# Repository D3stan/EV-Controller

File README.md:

# EV-Controller

This project is an ESP8266/ESP32-based exhaust valve controller for motorcycles. It offers real-time monitoring and configuration through a web interface, utilizing WebSockets for live data communication. The core functionality is to control the motorcycle's exhaust valve based on configurable RPM thresholds.

<table>
  <tr>
    <td>
      <br>
      
    </td>
    <td>
      
    </td>
  </tr>
</table>

## Features

- RPM-based exhaust valve control with configurable opening and closing thresholds.
- Web interface for real-time RPM monitoring and settings adjustment.
- WiFi Access Point (AP) mode for initial setup and configuration.
- WiFi Station (STA) mode to connect to an existing wireless network.
- Secure Over-the-Air (OTA) updates for both firmware and filesystem.
- Manual override for valve control directly from the web interface.

## Hardware Construction

To build the hardware, you will need to manufacture the PCB and source the electronic components.

### 1. PCB Manufacturing

The Gerber files required for PCB production are located in the `pcb/production/gerber.zip` archive. You can upload this file to any PCB manufacturer of your choice.

### 2. Component Sourcing

The list of all necessary components (Bill of Materials) is available in the `pcb/production/bom.csv` file. This file can be used to order parts from electronic component distributors.

### 3. Assembly

Solder the components onto the manufactured PCB. For component placement and orientation, please refer to the following files:

- **Schematic:** `pcb/schema.pdf`
- **KiCad Project:** `pcb/Rave-Controller.kicad_pro` (can be opened with KiCad)

For automated pick-and-place assembly, the `pcb/production/positions.csv` file is also provided.

## Firmware Installation

The firmware is built using PlatformIO.

### Prerequisites

- [Visual Studio Code](https://code.visualstudio.com/)
- [PlatformIO IDE extension](https://platformio.org/install/ide?install=vscode) for VS Code

### Build and Upload

1.  Clone this repository to your local machine.
2.  Open the cloned repository folder in Visual Studio Code.
3.  PlatformIO will automatically detect the `platformio.ini` file and prompt you to install the required project dependencies.
4.  Once dependencies are installed, select the correct environment for your board (e.g., `d1_mini`).
5.  Use the PlatformIO "Upload" task to build and flash the firmware to your device. Alternatively, you can run the following command from the integrated terminal:
    ```bash
    pio run -e d1_mini --target upload
    ```

## Initial Setup

1.  On the first boot, the device will create a Wi-Fi Access Point. The default SSID and password can be found in the source code (`data/config.json`).
2.  Connect your computer or smartphone to this Wi-Fi network.
3.  Open a web browser and navigate to the device's default IP address, which is `42.42.42.42`.
4.  From the web interface, you can configure your home Wi-Fi credentials (SSID and password) and set the desired RPM thresholds for the exhaust valve operation.
5.  After saving the new settings, the device will restart, connect to your specified Wi-Fi network, and begin normal operation.

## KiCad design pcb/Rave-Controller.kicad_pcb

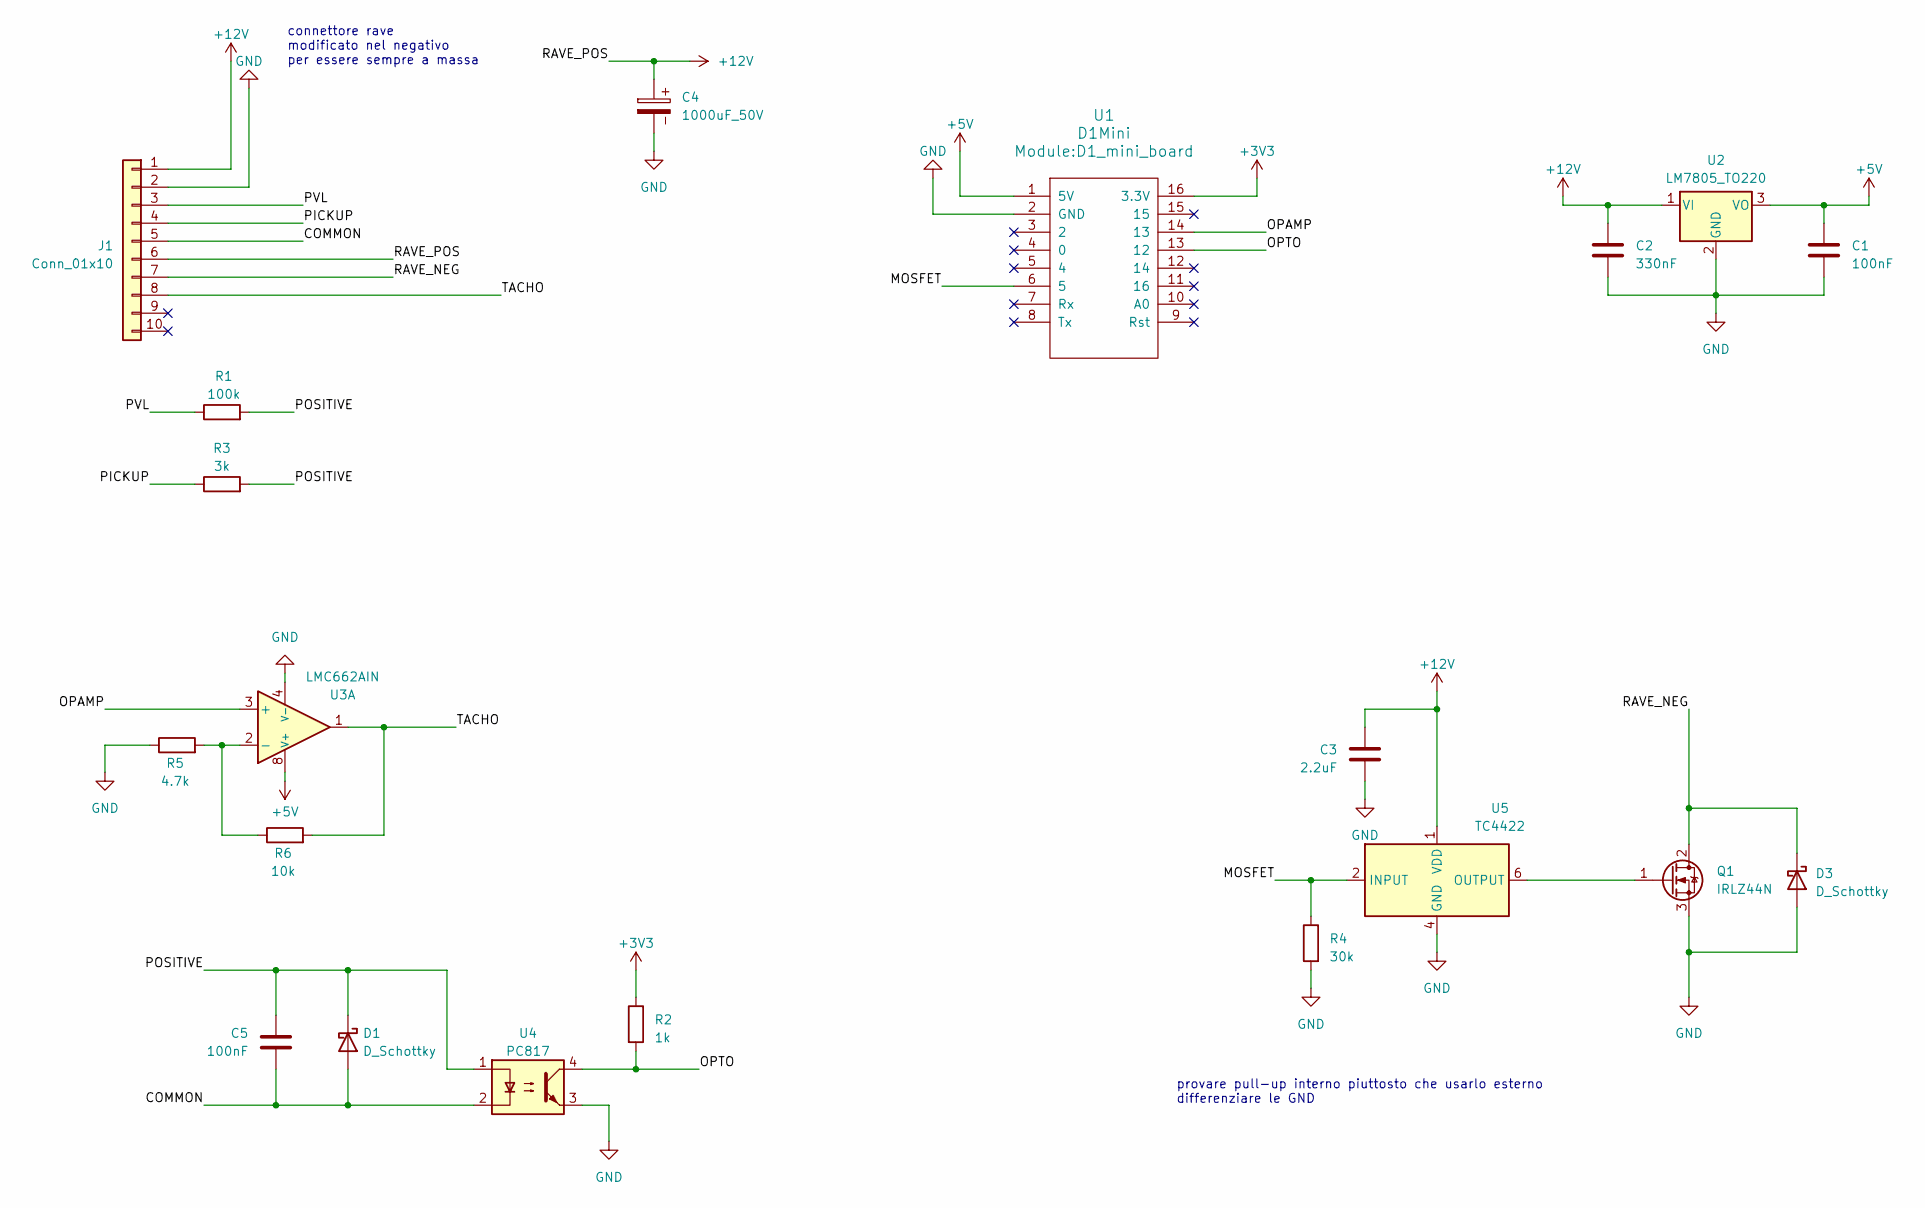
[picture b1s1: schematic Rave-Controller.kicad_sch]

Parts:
C1, C5: 100nF; C_Disc_D4.3mm_W1.9mm_P5.00mm
C2: 330nF; C_Disc_D4.3mm_W1.9mm_P5.00mm
C3: 2.2uF; C_Disc_D4.3mm_W1.9mm_P5.00mm
C4: 1000uF_50V; CP_Radial_D10.0mm_P7.50mm
D1, D3: D_Schottky; D_DO-34_SOD68_P7.62mm_Horizontal
J1: Conn_01x10; Molex_Mini-Fit_Jr_5569-10A2_2x05_P4.20mm_Horizontal
Q1: IRLZ44N; TO-220-3_Vertical
R1: 100k; R_Axial_DIN0204_L3.6mm_D1.6mm_P7.62mm_Horizontal
R2: 1k; R_Axial_DIN0204_L3.6mm_D1.6mm_P7.62mm_Horizontal
R3: 3k; R_Axial_DIN0204_L3.6mm_D1.6mm_P7.62mm_Horizontal
R4: 30k; R_Axial_DIN0204_L3.6mm_D1.6mm_P7.62mm_Horizontal
R5: 4.7k; R_Axial_DIN0204_L3.6mm_D1.6mm_P7.62mm_Horizontal
R6: 10k; R_Axial_DIN0204_L3.6mm_D1.6mm_P7.62mm_Horizontal
U1: D1Mini; D1_mini_board
U2: LM7805_TO220; TO-220-3_Vertical
U3: LMC662AIN; DIP-8_W7.62mm_LongPads
U4: PC817; DIP-4_W7.62mm
U5: TC4422; DIP-8_W7.62mm

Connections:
+3V3: R2.1, U1.16 (3.3V)
+5V: C1.1, U1.1 (5V), U2.3 (VO), U3.8 (V+)
+12V: C2.1, C3.2, C4.1, J1.1, J1.6, U2.1 (VI), U5.1 (VDD), U5.8 (VDD)
/COMMON: C5.1, D1.2 (A), J1.5, U4.2
/MOSFET: R4.1, U1.6 (5), U5.2 (INPUT)
/OPAMP: U1.14 (13), U3.3 (+); also elsewhere on the board
/OPTO: R2.2, U1.13 (12), U4.4
/PICKUP: J1.4, R3.1
/POSITIVE: C5.2, D1.1 (K), R1.2, R3.2, U4.1
/PVL: J1.3, R1.1
/RAVE_NEG: D3.1 (K), J1.7, Q1.2 (D)
/TACHO: J1.8, R6.2, U3.1
GND: C1.2, C2.2, C3.1, C4.2, D3.2 (A), J1.2, Q1.3 (S), R4.2, R5.1, U1.2 (GND), U2.2 (GND), U3.4 (V-), U4.3, U5.4 (GND), U5.5 (GND); also elsewhere on the board
unnamed: Q1.1 (G), U5.6 (OUTPUT), U5.7 (OUTPUT)
unnamed: R5.2, R6.1, U3.2 (-)

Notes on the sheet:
connettore rave modificato nel negativo per essere sempre a massa
provare pull-up interno piuttosto che usarlo esterno differenziare le GND

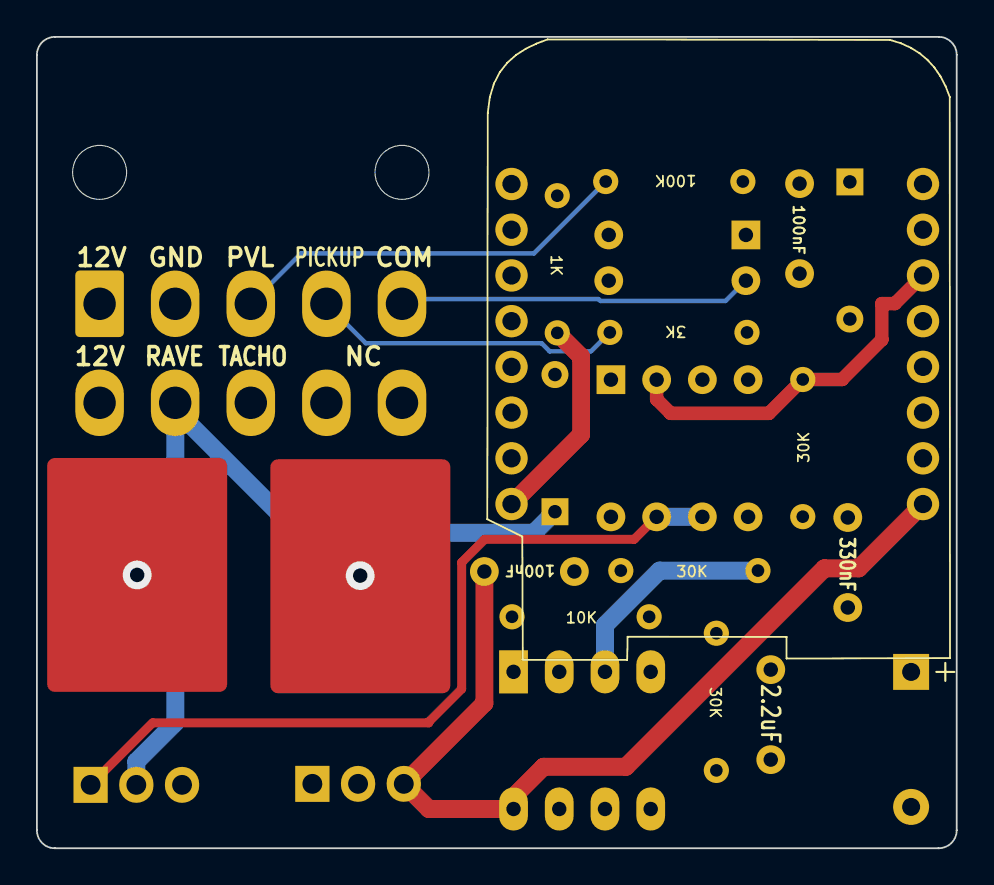
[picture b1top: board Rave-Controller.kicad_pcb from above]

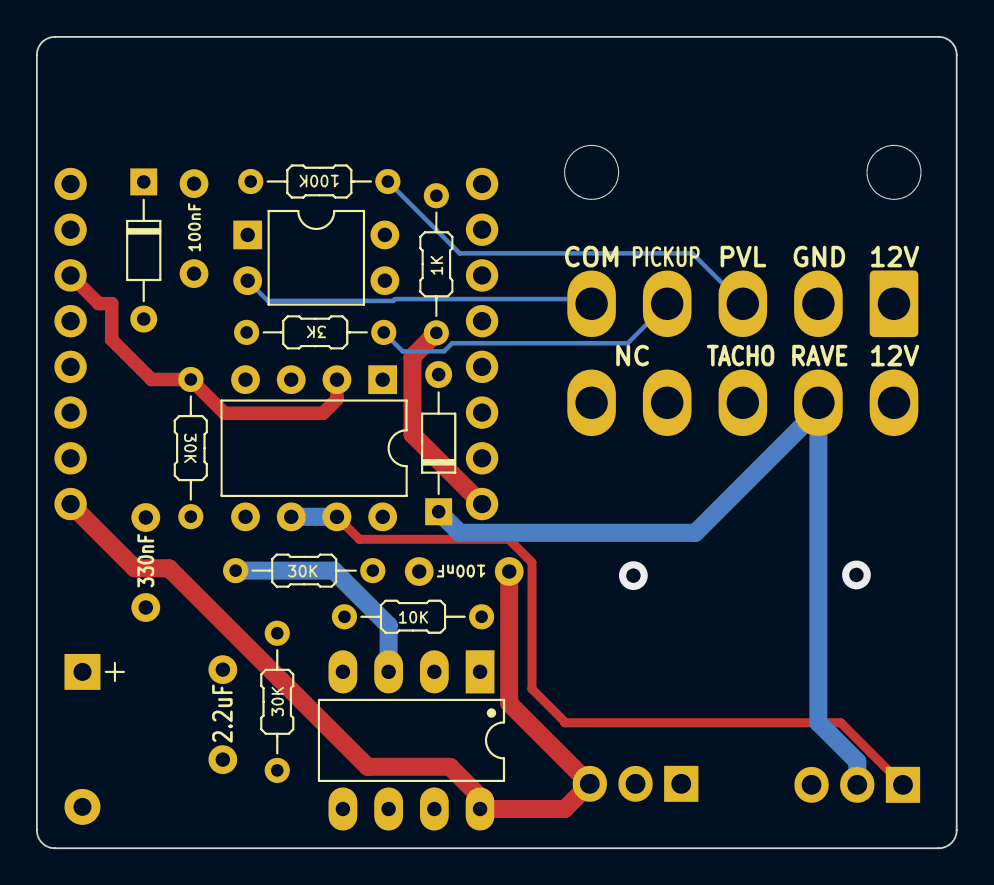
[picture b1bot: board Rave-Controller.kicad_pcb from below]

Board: 4 copper layers, 51.1 x 45.1 mm, 21 parts (16 on the bottom side), 15 nets.

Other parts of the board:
R7: 30k; R_Axial_DIN0204_L3.6mm_D1.6mm_P7.62mm_Horizontal

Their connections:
/OPAMP: R7.1; also elsewhere on the board
GND: R7.2; also elsewhere on the board

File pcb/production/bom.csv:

Designator,Footprint,Quantity,Value,LCSC Part #
"C1, C5",C_Disc_D4.3mm_W1.9mm_P5.00mm,2,100nF,
C2,C_Disc_D4.3mm_W1.9mm_P5.00mm,1,330nF,
C3,C_Disc_D4.3mm_W1.9mm_P5.00mm,1,2.2uF,
C4,CP_Radial_D10.0mm_P7.50mm,1,1000uF_50V,
"D1, D3",D_DO-34_SOD68_P7.62mm_Horizontal,2,D_Schottky,
J1,Molex_Mini-Fit_Jr_5569-10A2_2x05_P4.20mm_Horizontal,1,Conn_01x10,
Q1,TO-220-3_Vertical,1,IRLZ44N,
R1,R_Axial_DIN0204_L3.6mm_D1.6mm_P7.62mm_Horizontal,1,100k,
R2,R_Axial_DIN0204_L3.6mm_D1.6mm_P7.62mm_Horizontal,1,1k,
R3,R_Axial_DIN0204_L3.6mm_D1.6mm_P7.62mm_Horizontal,1,3k,
"R4, R7",R_Axial_DIN0204_L3.6mm_D1.6mm_P7.62mm_Horizontal,2,30k,
R5,R_Axial_DIN0204_L3.6mm_D1.6mm_P7.62mm_Horizontal,1,4.7k,
R6,R_Axial_DIN0204_L3.6mm_D1.6mm_P7.62mm_Horizontal,1,10k,
U1,D1_mini_board,1,D1Mini,
U2,TO-220-3_Vertical,1,LM7805_TO220,
U3,DIP-8_W7.62mm_LongPads,1,LMC662AIN,
U4,DIP-4_W7.62mm,1,PC817,
U5,DIP-8_W7.62mm,1,TC4422,

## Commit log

2024-10-11 websocket mode
2024-10-16 VB joined
2024-10-16 added images
2024-10-16 Aggiunto funzione slider e nuovi settings div
2024-10-25 trasforming version
2024-10-25 not tracking .vscode
2024-10-25 dropdown menu for settings page, not sending data to mcu tho
2024-10-26 web UI done (just need to check little things)
2024-10-26 integrated web UI handling and Remote Update
2024-10-26 small fix pre test
2024-10-26 esp32 compatibility
2024-10-27 working without UI json changes
2024-10-27 new config struct, working base mcu, need to add general checks and a system to handle updating error in STA mode (should reboot in AP and display the error)
2024-10-27 playing around with .ini config
2024-10-27 STRINGS NOT CHARS* in json doc load and saving
2024-10-27 http update error handling
2024-10-27 v3 FW test
2024-10-27 tested but might have some bugs somewhere, overall works update and error messages
2024-10-28 fixed reboot update crash using Ticker
2024-10-28 multiple file implementation
2024-10-28 small interface fixes
2024-10-28 fix header files and added rave file
2024-10-28 added rave headers
2024-10-28 engine off detection
2024-10-28 strange crash when connecting, happens only in release mode (not debug)
2024-10-29 prova
2024-10-29 UI update (from master)
2024-10-29 Crash problem: crashes only in release mode (debug works fine)
2024-10-29 update completed
2024-10-29 should work on a normal board (here analowrite doesnt work)
2024-10-30 wasnt a board problem but the checkIfEngineRunnig (not even the dns) was spamming, now working correctly
2024-10-30 fixed but without dns
2024-10-31 added hysteresis time control, other minor fixed (VERSION NOT TESTED)
2024-11-01 fixed string conversion problem, working and updated with lastMessage function
2024-11-01 tested with small solenoid and AWG, working, then added manual rave operation (UNTESTED)
2024-11-05 need to implement tacho
2024-11-05 trying to fix fixable errors
2024-11-06 update on s2 mini working, NO analog out
2024-11-06 analog done with retrocompatibility with esp8266, need to test with oscilloscope
2025-11-10 added old logs
2025-11-10 added documentation and PCB schematic
2025-11-10 added README and license
2025-11-10 pages
2025-11-10 demo for pages
2025-11-10 changed name for better explanation
